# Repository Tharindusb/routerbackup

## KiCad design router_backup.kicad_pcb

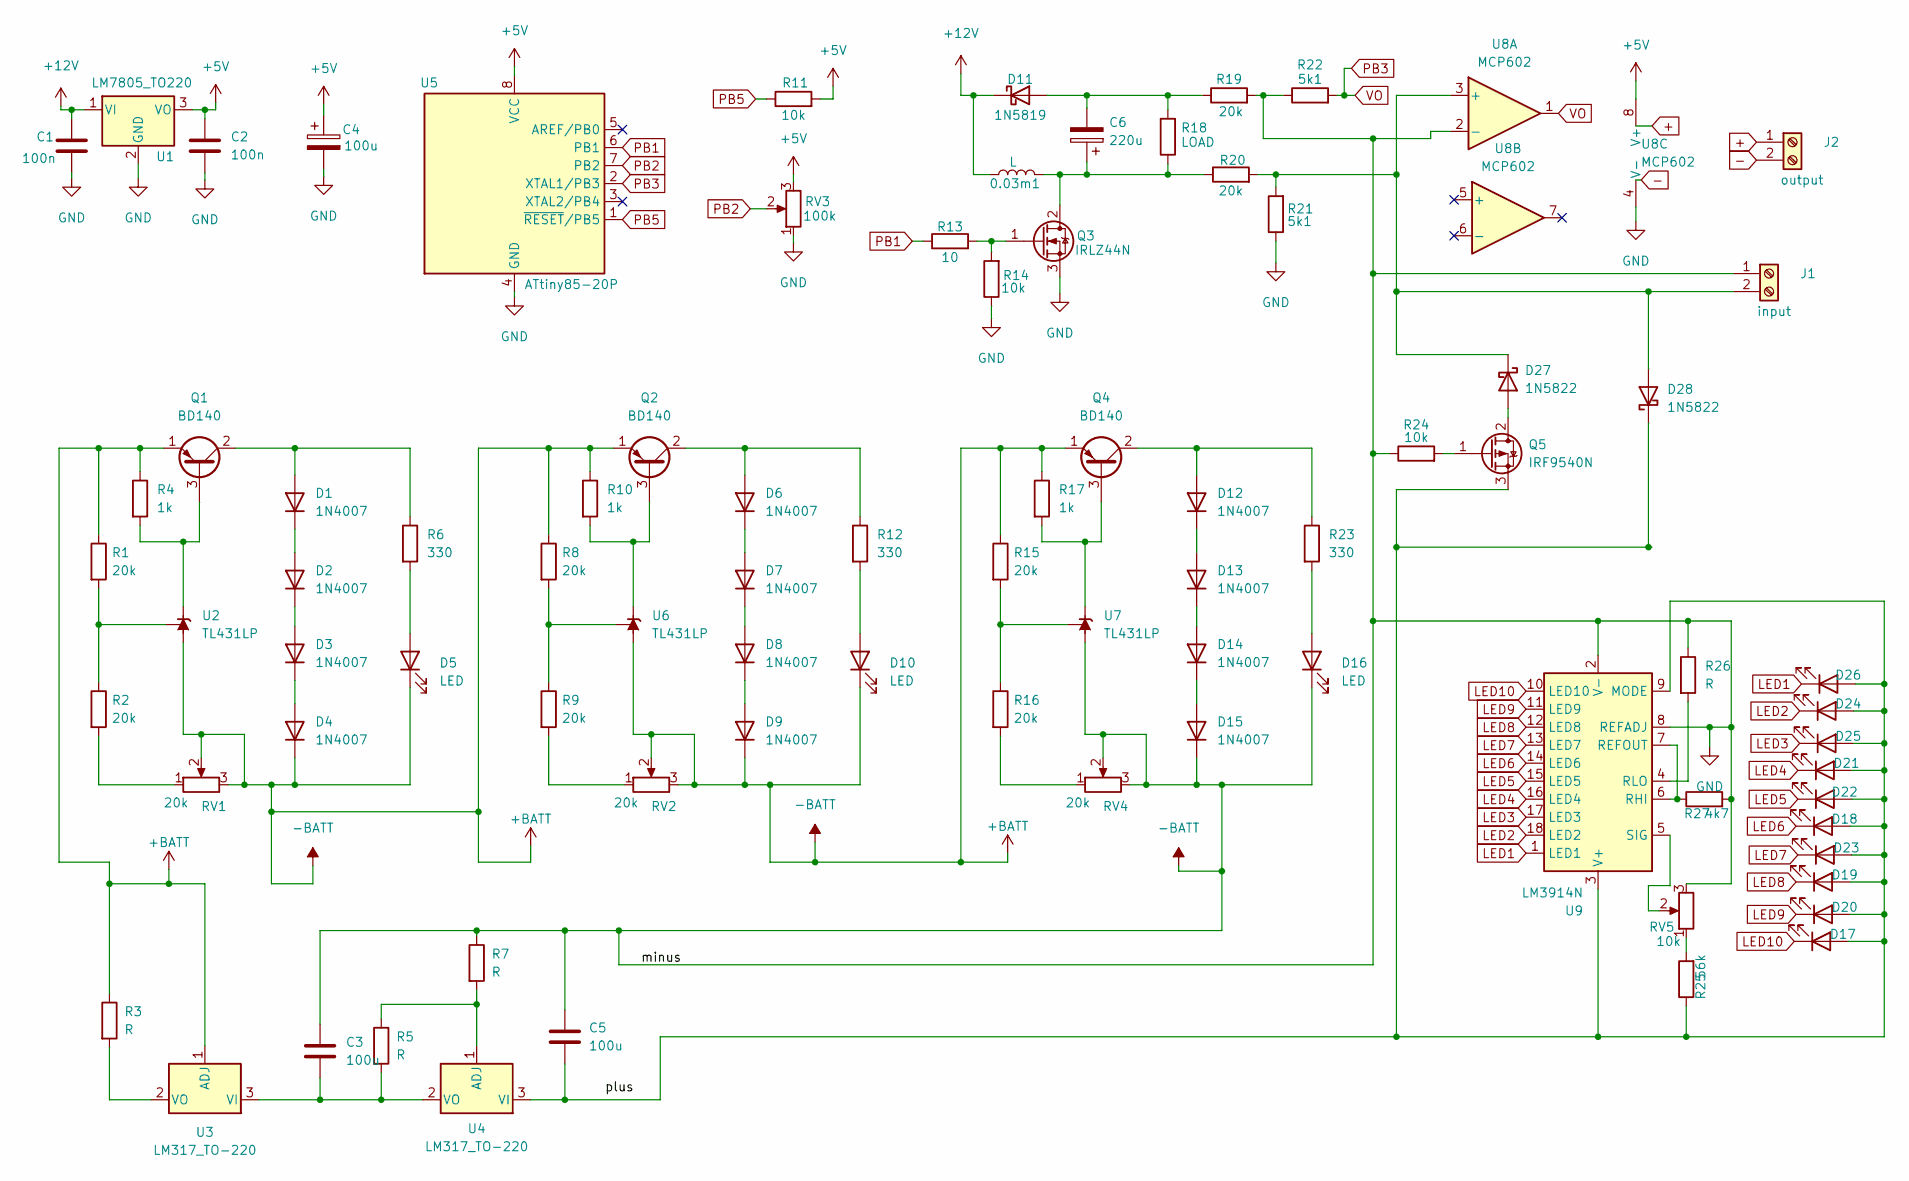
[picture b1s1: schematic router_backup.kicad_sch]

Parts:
0.03m1: L; L_6.3x6.3_H3
C1, C2: 100n; C_Radial_D4.0mm_H5.0mm_P1.50mm
C3: 100u; C_Radial_D4.0mm_H5.0mm_P1.50mm
C4: 100u; CP_Radial_D4.0mm_P1.50mm
C5: 100u; C_Radial_D4.0mm_H7.0mm_P1.50mm
C6: 220u; CP_Radial_D4.0mm_P1.50mm
D1, D2, D3, D4, D6, D7, D8, D9, D12, D13, D14, D15: 1N4007; D_DO-41_SOD81_P10.16mm_Horizontal
D5, D10, D16, D17, D18, D19, D20, D21, D22, D23, D24, D25, D26: LED; LED_Rectangular_W3.0mm_H2.0mm
D11: 1N5819; D_DO-41_SOD81_P10.16mm_Horizontal
D27, D28: 1N5822; D_DO-201AD_P15.24mm_Horizontal
J1: input; TerminalBlock_Phoenix_MKDS-1,5-2-5.08_1x02_P5.08mm_Horizont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
J2: output; TerminalBlock_Phoenix_MKDS-1,5-2-5.08_1x02_P5.08mm_Horizont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
Q1, Q2, Q4: BD140; TO-126-3_Vertical
Q3: IRLZ44N; TO-220-3_Vertical
Q5: IRF9540N; TO-220-3_Vertical
R1, R2, R8, R9, R15, R16, R19, R20: 20k; R_Axial_DIN0309_L9.0mm_D3.2mm_P12.70mm_Horizontal
R3, R5, R7, R26: R; R_Axial_DIN0309_L9.0mm_D3.2mm_P12.70mm_Horizontal
R4, R10, R17: 1k; R_Axial_DIN0309_L9.0mm_D3.2mm_P12.70mm_Horizontal
R6, R12, R23: 330; R_Axial_DIN0309_L9.0mm_D3.2mm_P12.70mm_Horizontal
R11, R14, R24: 10k; R_Axial_DIN0309_L9.0mm_D3.2mm_P12.70mm_Horizontal
R13: 10; R_Axial_DIN0309_L9.0mm_D3.2mm_P12.70mm_Horizontal
R18: LOAD; R_Axial_DIN0309_L9.0mm_D3.2mm_P12.70mm_Horizontal
R21, R22: 5k1; R_Axial_DIN0309_L9.0mm_D3.2mm_P12.70mm_Horizontal
R25: 56k; R_Axial_DIN0309_L9.0mm_D3.2mm_P12.70mm_Horizontal
R27: 4k7; R_Axial_DIN0309_L9.0mm_D3.2mm_P12.70mm_Horizontal
RV1, RV2, RV4: 20k; Potentiometer_Bourns_3266Y_Vertical
RV3: 100k; Potentiometer_Bourns_3266Y_Vertical
RV5: 10k; Potentiometer_Bourns_3266Y_Vertical
U1: LM7805_TO220; TO-220-3_Vertical
U2, U6, U7: TL431LP; TO-92_Inline
U3, U4: LM317_TO-220; TO-220-3_Vertical
U5: ATtiny85-20P; DIP-8_W7.62mm
U8: MCP602; R_Array_SIP8
U9: LM3914N; DIP-18_W7.62mm

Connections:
+: J2.1
+5V: C2.1, C4.1, R11.2, RV3.3, U1.3 (VO), U5.8 (VCC), U8.8 (V+)
+12V: 0.03m1.1, C1.1, D11.1 (K), U1.1 (VI)
+BATT: C1.2, C2.2, C3.1, C4.2, C5.1, D4.1 (K), D5.1 (K), D9.1 (K), D10.1 (K), D15.1 (K), D16.1 (K), J1.1, Q1.1 (E), Q2.1 (E), Q3.3 (S), Q4.1 (E), R1.1, R3.1, R4.1, R7.1, R8.1, R10.1, R14.1, R15.1, R17.1, R19.2, R21.1, R22.1, R24.1, R26.1, R27.2, RV1.2, RV1.3, RV2.2, RV2.3, RV3.1, RV4.2, RV4.3, RV5.3, U1.2 (GND), U2.2 (A), U3.1 (ADJ), U5.4 (GND), U6.2 (A), U7.2 (A), U8.2 (-), U8.4 (V-), U9.2 (V-), U9.8 (REFADJ)
-: J2.2
LED1: D26.1 (K), U9.1 (LED1)
LED2: D24.1 (K), U9.18 (LED2)
LED3: D25.1 (K), U9.17 (LED3)
LED4: D21.1 (K), U9.16 (LED4)
LED5: D22.1 (K), U9.15 (LED5)
LED6: D18.1 (K), U9.14 (LED6)
LED7: D23.1 (K), U9.13 (LED7)
LED8: D19.1 (K), U9.12 (LED8)
LED9: D20.1 (K), U9.11 (LED9)
LED10: D17.1 (K), U9.10 (LED10)
unnamed: 0.03m1.2, C6.1, Q3.2 (D), R18.1, R20.1
unnamed: C3.2, R5.2, U3.3 (VI), U4.2 (VO)
unnamed: C5.2, D17.2 (A), D18.2 (A), D19.2 (A), D20.2 (A), D21.2 (A), D22.2 (A), D23.2 (A), D24.2 (A), D25.2 (A), D26.2 (A), D28.1 (K), Q5.3 (S), R25.1, U4.3 (VI), U9.3 (V+), U9.9 (MODE)
unnamed: C6.2, D11.2 (A), R18.2, R19.1
unnamed: D1.1 (K), D2.2 (A)
unnamed: D1.2 (A), Q1.2 (C), R6.1
unnamed: D2.1 (K), D3.2 (A)
unnamed: D3.1 (K), D4.2 (A)
unnamed: D5.2 (A), R6.2
unnamed: D6.1 (K), D7.2 (A)
unnamed: D6.2 (A), Q2.2 (C), R12.1
unnamed: D7.1 (K), D8.2 (A)
unnamed: D8.1 (K), D9.2 (A)
unnamed: D10.2 (A), R12.2
unnamed: D12.1 (K), D13.2 (A)
unnamed: D12.2 (A), Q4.2 (C), R23.1
unnamed: D13.1 (K), D14.2 (A)
unnamed: D14.1 (K), D15.2 (A)
unnamed: D16.2 (A), R23.2
unnamed: D27.1 (K), D28.2 (A), J1.2, R20.2, R21.2, U8.3 (+)
unnamed: Q1.3 (B), R4.2, U2.3 (K)
unnamed: Q2.3 (B), R10.2, U6.3 (K)
unnamed: Q3.1 (G), R13.2, R14.2
unnamed: Q4.3 (B), R17.2, U7.3 (K)
unnamed: Q5.1 (G), R24.2
unnamed: D27.2 (A), Q5.2 (D)
unnamed: R1.2, R2.1, U2.1 (REF)
unnamed: R2.2, RV1.1
unnamed: R3.2, U3.2 (VO)
unnamed: R5.1, R7.2, U4.1 (ADJ)
unnamed: R8.2, R9.1, U6.1 (REF)
unnamed: R9.2, RV2.1
unnamed: R15.2, R16.1, U7.1 (REF)
unnamed: R16.2, RV4.1
unnamed: R25.2, RV5.1
unnamed: R26.2, U9.4 (RLO)
unnamed: RV5.2, U9.5 (SIG)
unnamed: R27.1, U9.6 (RHI), U9.7 (REFOUT)
PB1: R13.1, U5.6 (PB1)
PB2: RV3.2, U5.7 (PB2)
PB3: R22.2, U5.2 (XTAL1/PB3), U8.1
PB5: R11.1, U5.1 (~RESET/PB5)

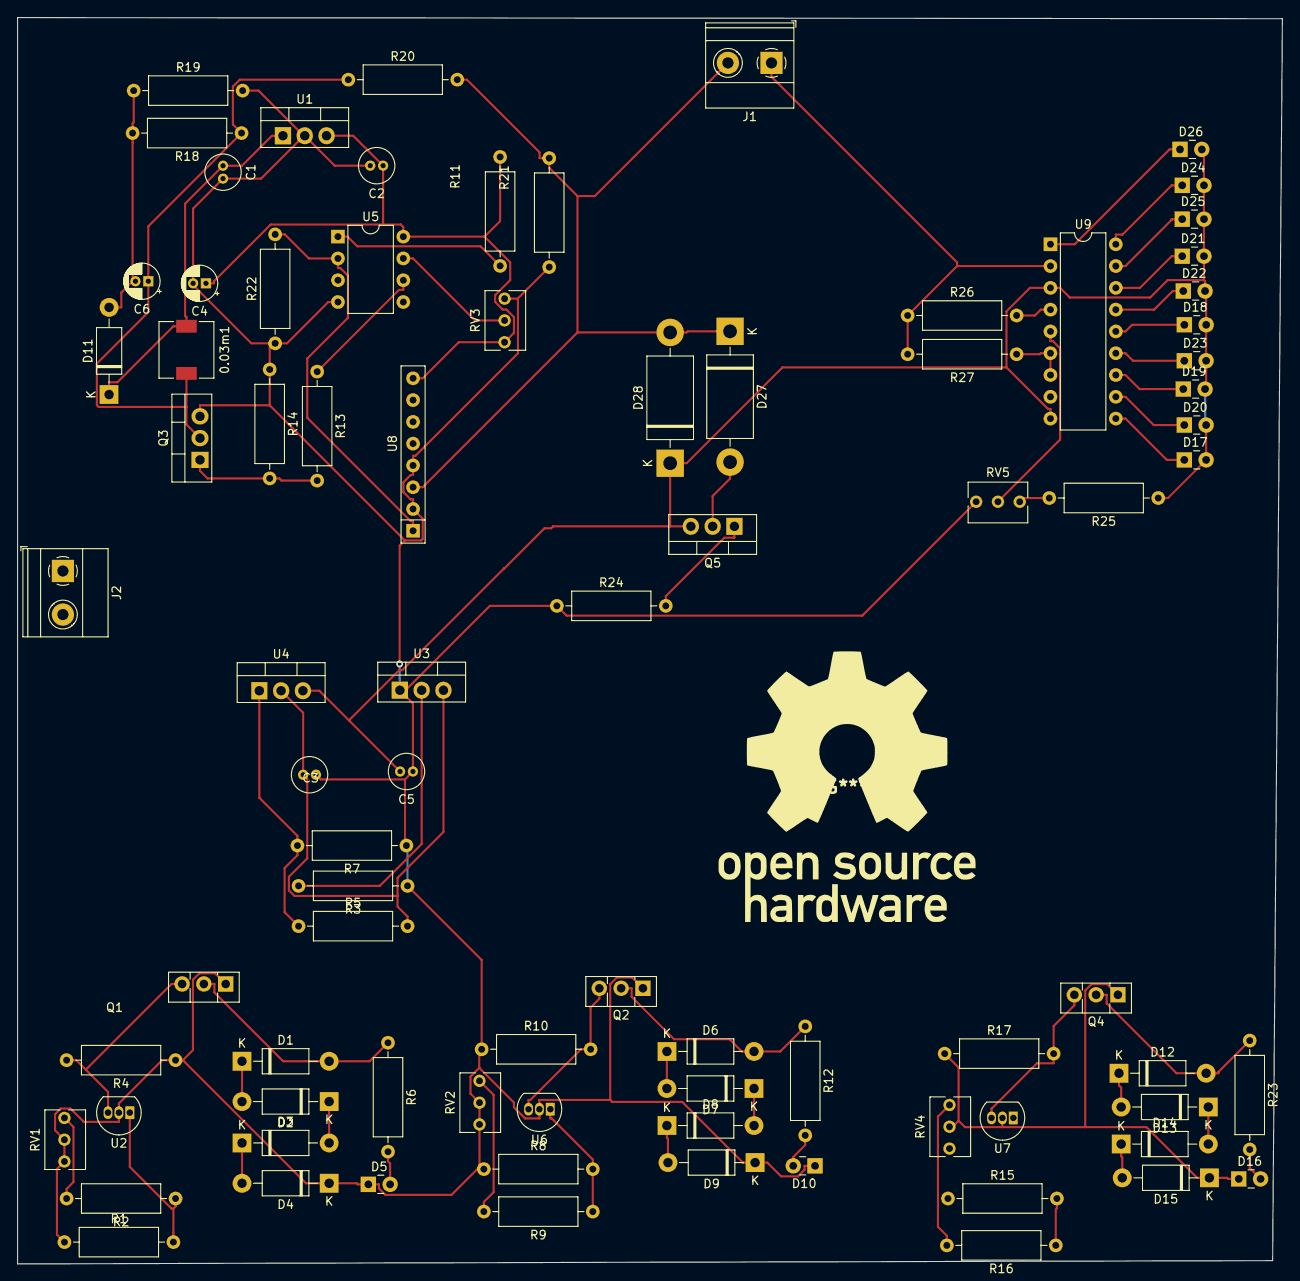
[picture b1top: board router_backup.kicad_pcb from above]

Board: 2 copper layers, 147.4 x 145.3 mm, 83 parts (0 on the bottom side), 55 nets.

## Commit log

2022-07-15 Buck converter
2022-07-16 edited readme
2022-07-16 added indicator
2022-07-19 added .gitignore
2022-07-19 updated pcb
